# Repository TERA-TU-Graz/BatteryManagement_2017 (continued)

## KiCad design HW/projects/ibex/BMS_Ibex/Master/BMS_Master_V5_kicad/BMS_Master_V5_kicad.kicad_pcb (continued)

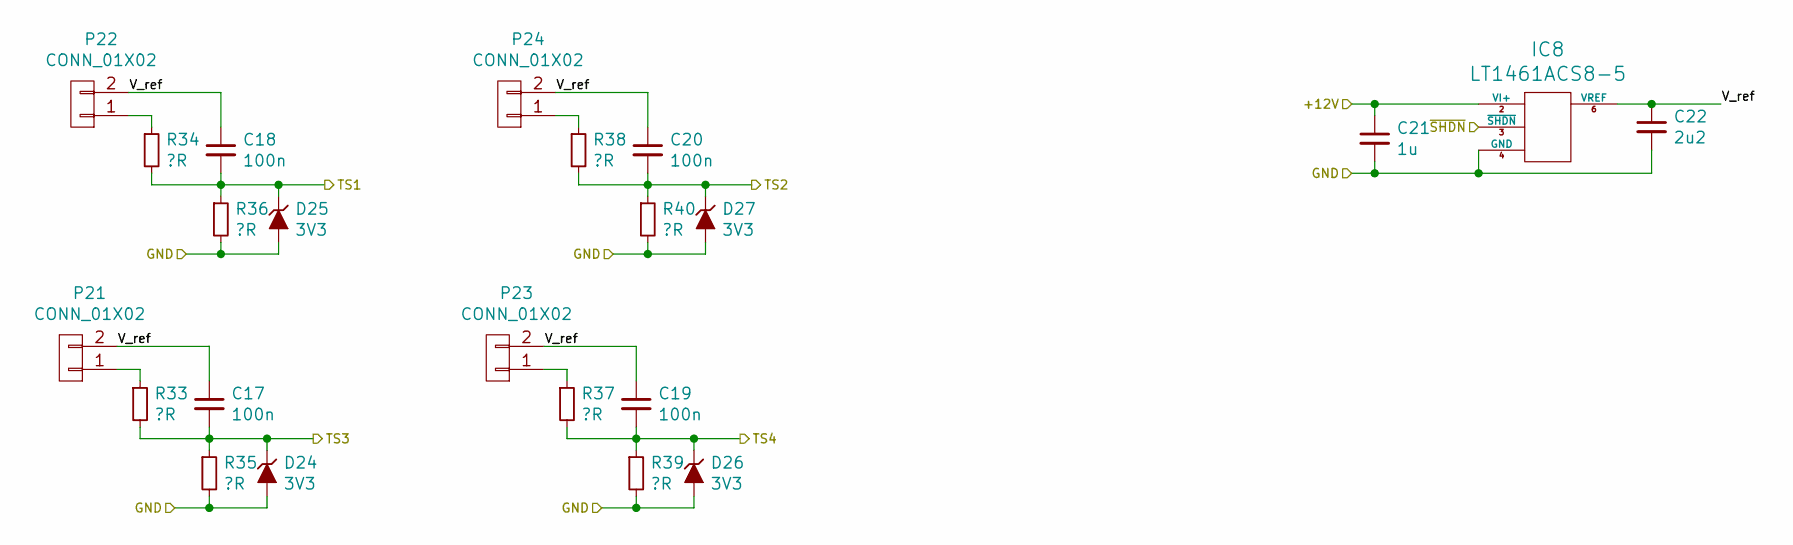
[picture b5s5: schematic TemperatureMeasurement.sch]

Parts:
C17, C18, C19, C20: 100n; C_0603
C21: 1u; C_0805
C22: 2u2; C_0805
D24, D25, D26, D27: 3V3; DO-216AA
IC8: LT1461ACS8-5; SOIC-8_3.9x4.9mm_Pitch1.27mm
P21, P22, P23, P24: CONN_01X02; Molex_PicoBlade_53398-0271
R33, R34, R35, R36, R37, R38, R39, R40: ?R; R_0603

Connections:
+12V: C21.1, IC8.2 (VI+); also elsewhere on the board
/TS1: C18.2, D25.1 (K), R34.2, R36.1; also elsewhere on the board
/TS2: C20.2, D27.1 (K), R38.2, R40.1; also elsewhere on the board
/TS3: C17.2, D24.1 (K), R33.2, R35.1; also elsewhere on the board
/TS4: C19.2, D26.1 (K), R37.2, R39.1; also elsewhere on the board
/TemperatureMeasurement/V_ref: C17.1, C18.1, C19.1, C20.1, C22.1, IC8.6 (VREF), P21.2, P22.2, P23.2, P24.2
/TemperatureMeasurement/~SHDN: IC8.3 (~SHDN); also elsewhere on the board
GND: C21.2, C22.2, D24.2 (A), D25.2 (A), D26.2 (A), D27.2 (A), IC8.4 (GND), R35.2, R36.2, R39.2, R40.2; also elsewhere on the board
unnamed: P21.1, R33.1
unnamed: P22.1, R34.1
unnamed: P23.1, R37.1
unnamed: P24.1, R38.1

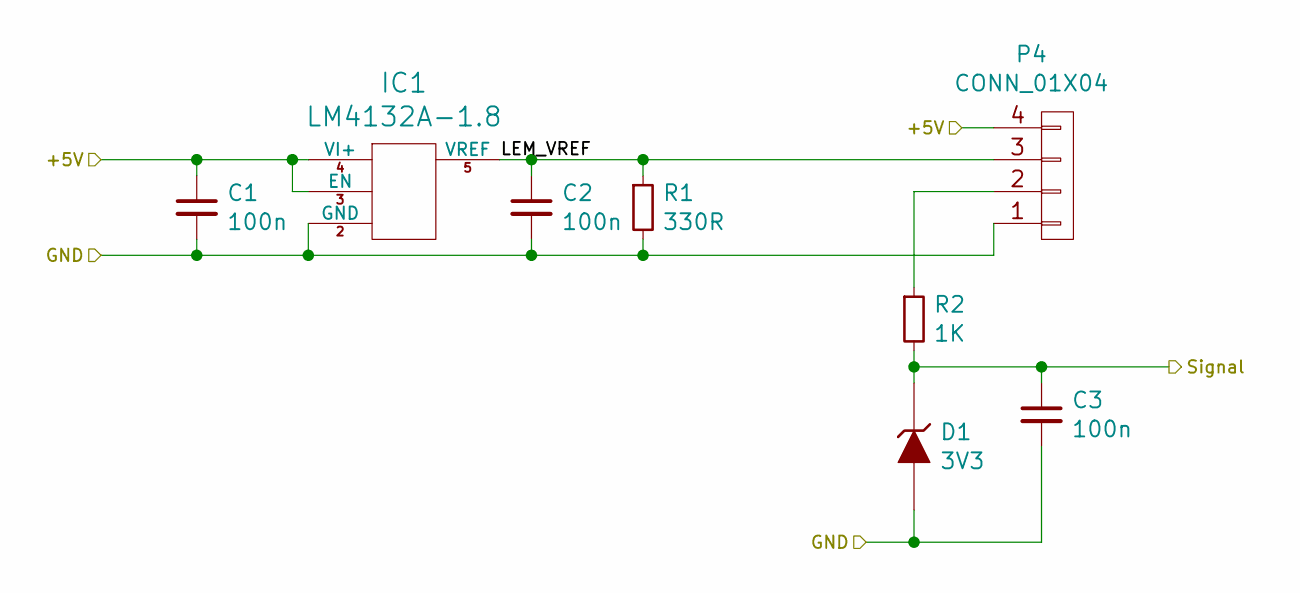
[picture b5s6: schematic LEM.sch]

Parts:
C1, C2, C3: 100n; C_0603
D1: 3V3; DO-216AA
IC1: LM4132A-1.8; SOT-23-5
P4: CONN_01X04; Molex_PicoBlade_53398-0471
R1: 330R; R_0603
R2: 1K; R_0805

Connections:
+5V: C1.1, IC1.3 (EN), IC1.4 (VI+), P4.4; also elsewhere on the board
/CurrentMeasurement/LEM1/LEM_VREF: C2.1, IC1.5 (VREF), P4.3, R1.1
/LEM1: C3.1, D1.1 (K), R2.2; also elsewhere on the board
GND: C1.2, C2.2, C3.2, D1.2 (A), IC1.2 (GND), P4.1, R1.2; also elsewhere on the board
unnamed: P4.2, R2.1

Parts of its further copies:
C4, C5, C6, C7, C8, C9: 100n; C_0603
D2, D3: 3V3; DO-216AA
IC2, IC3: LM4132A-1.8; SOT-23-5
P5, P6: CONN_01X04; Molex_PicoBlade_53398-0471
R3, R5: 330R; R_0603
R4, R6: 1K; R_0805

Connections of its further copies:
+5V: C4.1, C7.1, IC2.3 (EN), IC2.4 (VI+), IC3.3 (EN), IC3.4 (VI+), P5.4, P6.4; also elsewhere on the board
/CurrentMeasurement/LEM2/LEM_VREF: C5.1, IC2.5 (VREF), P5.3, R3.1
/CurrentMeasurement/LEM3/LEM_VREF: C8.1, IC3.5 (VREF), P6.3, R5.1
/LEM2: C6.1, D2.1 (K), R4.2; also elsewhere on the board
/LEM3: C9.1, D3.1 (K), R6.2; also elsewhere on the board
GND: C4.2, C5.2, C6.2, C7.2, C8.2, C9.2, D2.2 (A), D3.2 (A), IC2.2 (GND), IC3.2 (GND), P5.1, P6.1, R3.2, R5.2; also elsewhere on the board
unnamed: P5.2, R4.1
unnamed: P6.2, R6.1

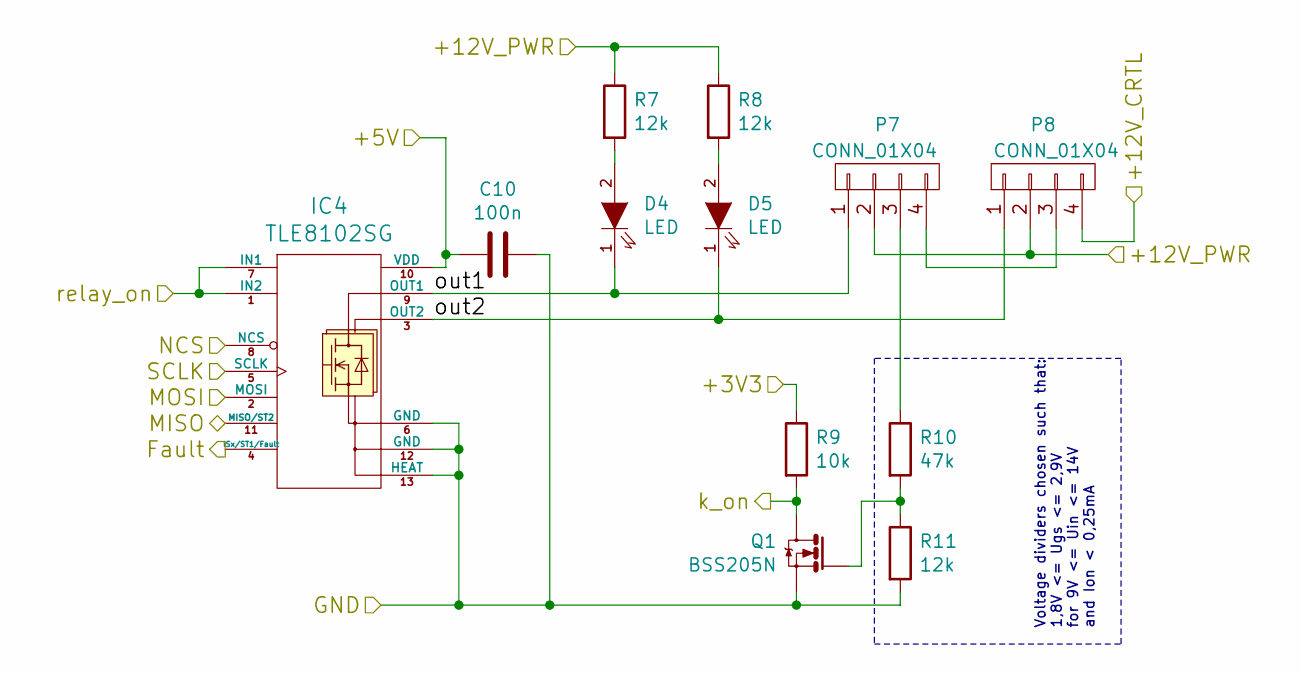
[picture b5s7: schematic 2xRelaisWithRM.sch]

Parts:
C10: 100n; C_0603
D4, D5: LED; LED_0805
IC4: TLE8102SG; INF-PG-DSO-12-11-EP_EPvias
P7, P8: CONN_01X04; JST_XH_B04B-XH-A_04x2.50mm_Straight
Q1: BSS205N; SOT-23
R7, R8, R11: 12k; R_0805
R9: 10k; R_0805
R10: 47k; R_0805

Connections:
+3V3: R9.1; also elsewhere on the board
+5V: C10.2, IC4.10 (VDD); also elsewhere on the board
+12L: P7.2, P8.2, R7.1, R8.1; also elsewhere on the board
+12V: P8.4; also elsewhere on the board
/Interlock_OK: IC4.1 (IN2), IC4.7 (IN1); also elsewhere on the board
/MISO: IC4.11 (MISO/ST2); also elsewhere on the board
/MOSI: IC4.2 (MOSI); also elsewhere on the board
/RelayAndFanCtrl/SuperChargerRelais/out1: D4.1 (K), IC4.9 (OUT1), P7.1
/RelayAndFanCtrl/SuperChargerRelais/out2: D5.1 (K), IC4.3 (OUT2), P8.1
/SCLK: IC4.5 (SCLK); also elsewhere on the board
/SPI_Controller/NCS7: IC4.8 (NCS); also elsewhere on the board
/SuperCharger_Fault: IC4.4 (ISx/ST1/Fault); also elsewhere on the board
/SuperCharger_ON: Q1.3 (D), R9.2; also elsewhere on the board
GND: C10.1, IC4.6 (GND), IC4.12 (GND), IC4.13 (HEAT), Q1.2 (S), R11.2; also elsewhere on the board
unnamed: D4.2 (A), R7.2
unnamed: D5.2 (A), R8.2
unnamed: P7.3, R10.1
unnamed: P7.4, P8.3
unnamed: Q1.1 (G), R10.2, R11.1

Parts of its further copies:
C11: 100n; C_0603
D6, D7: LED; LED_0805
IC5: TLE8102SG; INF-PG-DSO-12-11-EP_EPvias
P9, P10: CONN_01X04; JST_XH_B04B-XH-A_04x2.50mm_Straight
Q2: BSS205N; SOT-23
R12, R13, R16: 12k; R_0805
R14: 10k; R_0805
R15: 47k; R_0805

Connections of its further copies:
+3V3: R14.1; also elsewhere on the board
+5V: C11.2, IC5.10 (VDD); also elsewhere on the board
+12L: P9.2, P10.2, R12.1, R13.1; also elsewhere on the board
+12V: P10.4; also elsewhere on the board
/Interlock_OK: IC5.1 (IN2), IC5.7 (IN1); also elsewhere on the board
/MISO: IC5.11 (MISO/ST2); also elsewhere on the board
/MOSI: IC5.2 (MOSI); also elsewhere on the board
/Main_Fault: IC5.4 (ISx/ST1/Fault); also elsewhere on the board
/Main_On: Q2.3 (D), R14.2; also elsewhere on the board
/RelayAndFanCtrl/MainRelais/out1: D6.1 (K), IC5.9 (OUT1), P9.1
/RelayAndFanCtrl/MainRelais/out2: D7.1 (K), IC5.3 (OUT2), P10.1
/SCLK: IC5.5 (SCLK); also elsewhere on the board
/SPI_Controller/NCS6: IC5.8 (NCS); also elsewhere on the board
GND: C11.1, IC5.6 (GND), IC5.12 (GND), IC5.13 (HEAT), Q2.2 (S), R16.2; also elsewhere on the board
unnamed: D6.2 (A), R12.2
unnamed: D7.2 (A), R13.2
unnamed: P9.3, R15.1
unnamed: P9.4, P10.3
unnamed: Q2.1 (G), R15.2, R16.1

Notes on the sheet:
Voltage dividers chosen such that: 1,8V <= Ugs <= 2,9V for 9V <= Uin <= 14V and Ion < 0,25mA

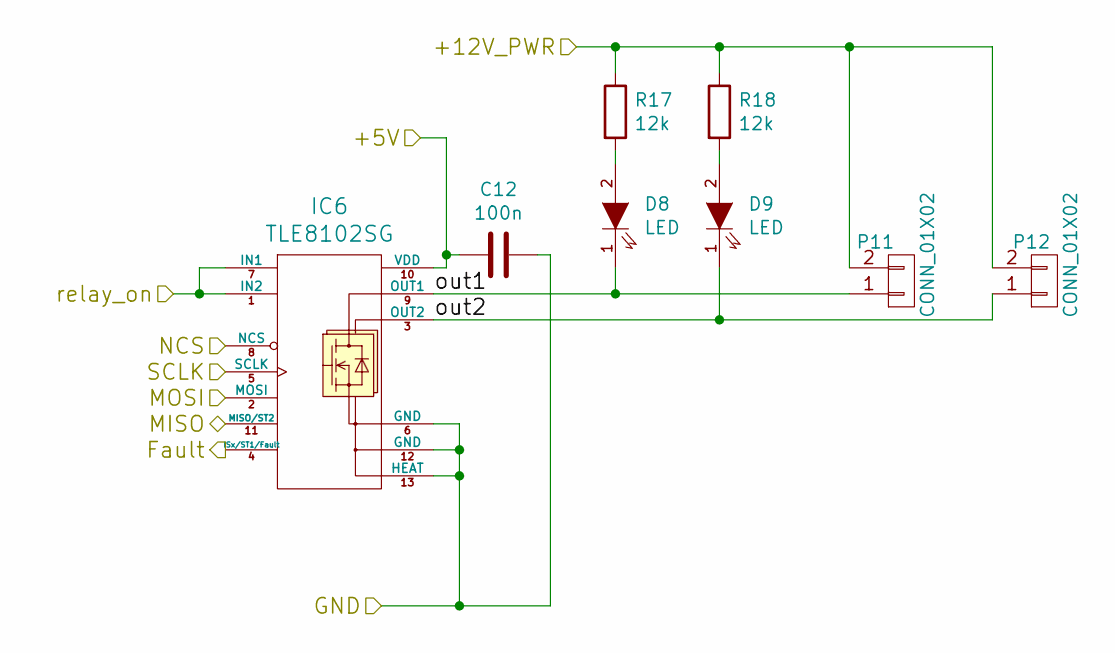
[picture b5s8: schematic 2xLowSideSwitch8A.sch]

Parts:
C12: 100n; C_0603
D8, D9: LED; LED_0805
IC6: TLE8102SG; INF-PG-DSO-12-11-EP_EPvias
P11, P12: CONN_01X02; JST_XH_B02B-XH-A_02x2.50mm_Straight
R17, R18: 12k; R_0805

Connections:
+5V: C12.2, IC6.10 (VDD); also elsewhere on the board
+12L: P11.2, P12.2, R17.1, R18.1; also elsewhere on the board
/Interlock_OK: IC6.1 (IN2), IC6.7 (IN1); also elsewhere on the board
/MISO: IC6.11 (MISO/ST2); also elsewhere on the board
/MOSI: IC6.2 (MOSI); also elsewhere on the board
/Precharge_Fault: IC6.4 (ISx/ST1/Fault); also elsewhere on the board
/RelayAndFanCtrl/PRECHARGER/out1: D8.1 (K), IC6.9 (OUT1), P11.1
/RelayAndFanCtrl/PRECHARGER/out2: D9.1 (K), IC6.3 (OUT2), P12.1
/SCLK: IC6.5 (SCLK); also elsewhere on the board
/SPI_Controller/NCS8: IC6.8 (NCS); also elsewhere on the board
GND: C12.1, IC6.6 (GND), IC6.12 (GND), IC6.13 (HEAT); also elsewhere on the board
unnamed: D8.2 (A), R17.2
unnamed: D9.2 (A), R18.2

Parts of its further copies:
C13: 100n; C_0603
D10, D11: LED; LED_0805
IC7: TLE8102SG; INF-PG-DSO-12-11-EP_EPvias
P13, P14: CONN_01X02; JST_XH_B02B-XH-A_02x2.50mm_Straight
R19, R20: 12k; R_0805

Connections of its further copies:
+5V: C13.2, IC7.10 (VDD); also elsewhere on the board
+12L: P13.2, P14.2, R19.1, R20.1; also elsewhere on the board
/FAN_Fault: IC7.4 (ISx/ST1/Fault); also elsewhere on the board
/FAN_PWM: IC7.1 (IN2), IC7.7 (IN1); also elsewhere on the board
/MISO: IC7.11 (MISO/ST2); also elsewhere on the board
/MOSI: IC7.2 (MOSI); also elsewhere on the board
/RelayAndFanCtrl/FANS/out1: D10.1 (K), IC7.9 (OUT1), P13.1
/RelayAndFanCtrl/FANS/out2: D11.1 (K), IC7.3 (OUT2), P14.1
/SCLK: IC7.5 (SCLK); also elsewhere on the board
/SPI_Controller/NCS5: IC7.8 (NCS); also elsewhere on the board
GND: C13.1, IC7.6 (GND), IC7.12 (GND), IC7.13 (HEAT); also elsewhere on the board
unnamed: D10.2 (A), R19.2
unnamed: D11.2 (A), R20.2

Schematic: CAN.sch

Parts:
C15: 47nF; C_0805
C23: 100n; C_0805
D12, D13: SUPPRESSOR; SOT-23
JP7, JP8: Jumper_NO_Small; SOLDERJUMPER_2
L1: CM_CHOKE; ACT45B-510-2P-TL003
P17: CAN_CON; CIOC_4-1-FV
R23: 56k; R_0805
R24, R25: 60R; R_0805
S1: SWITCH_02x2POS; TE_1825360-1
U3: SN65HVD230; SOIC-8_3.9x4.9mm_Pitch1.27mm

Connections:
/CAN1_RS: R23.2; also elsewhere on the board
/CAN1_RXD: U3.4 (RXD); also elsewhere on the board
/CAN1_TXD: U3.1 (TXD); also elsewhere on the board
/CAN_connect/CAN1/CAN+: D12.2 (Pin2), JP7.1, L1.3 (SA), U3.7 (CANH); also elsewhere on the board
/CAN_connect/CAN1/CAN-: D12.1 (Pin1), JP8.1, L1.2 (AB), U3.6 (CANL); also elsewhere on the board
/CAN_connect/CAN1/CAN_supply: C23.1, U3.3 (VCC); also elsewhere on the board
/CAN_connect/CAN1/CANperi+: D13.2 (Pin2), JP7.2, L1.4 (SB), P17.3 (CAN_H), S1.4
/CAN_connect/CAN1/CANperi-: D13.1 (Pin1), JP8.2, L1.1 (AA), P17.2 (CAN_L), S1.3
GND: C15.2, C23.2, D12.3 (Pin3), D13.3 (Pin3), P17.1 (GND), U3.2 (GND); also elsewhere on the board
unnamed: C15.1, R24.2, R25.2
unnamed: R23.1, U3.8 (Rs(Mode))
unnamed: R24.1, S1.1
unnamed: R25.1, S1.2

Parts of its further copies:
C16: 47nF; C_0805
C24: 100n; C_0805
D14, D15: SUPPRESSOR; SOT-23
JP9, JP10: Jumper_NO_Small; SOLDERJUMPER_2
L2: CM_CHOKE; ACT45B-510-2P-TL003
P18: CAN_CON; CIOC_4-1-FV
R26: 56k; R_0805
R27, R28: 60R; R_0805
S2: SWITCH_02x2POS; TE_1825360-1
U4: SN65HVD230; SOIC-8_3.9x4.9mm_Pitch1.27mm

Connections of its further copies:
+3V3: C24.1, U4.3 (VCC); also elsewhere on the board
/CAN2_RS: R26.2; also elsewhere on the board
/CAN2_RXD: U4.4 (RXD); also elsewhere on the board
/CAN2_TXD: U4.1 (TXD); also elsewhere on the board
/CAN_connect/CAN2/CAN+: D14.2 (Pin2), JP9.1, L2.3 (SA), U4.7 (CANH)
/CAN_connect/CAN2/CAN-: D14.1 (Pin1), JP10.1, L2.2 (AB), U4.6 (CANL)
/CAN_connect/CAN2/CANperi+: D15.2 (Pin2), JP9.2, L2.4 (SB), P18.3 (CAN_H), S2.4
/CAN_connect/CAN2/CANperi-: D15.1 (Pin1), JP10.2, L2.1 (AA), P18.2 (CAN_L), S2.3
GND: C16.2, C24.2, D14.3 (Pin3), D15.3 (Pin3), P18.1 (GND), U4.2 (GND); also elsewhere on the board
unnamed: C16.1, R27.2, R28.2
unnamed: R26.1, U4.8 (Rs(Mode))
unnamed: R27.1, S2.1
unnamed: R28.1, S2.2

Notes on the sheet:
RS(Mode): GND (Logic L) = Tranceiver on 3V3 (Logic H) = Tranceiver in power safe (standby = receive only)
Connection used for on board can tranceiver. (optional)
Place everything near the connector. (Exception CAN Tranceiver: this should be near STM)
keep this wires short

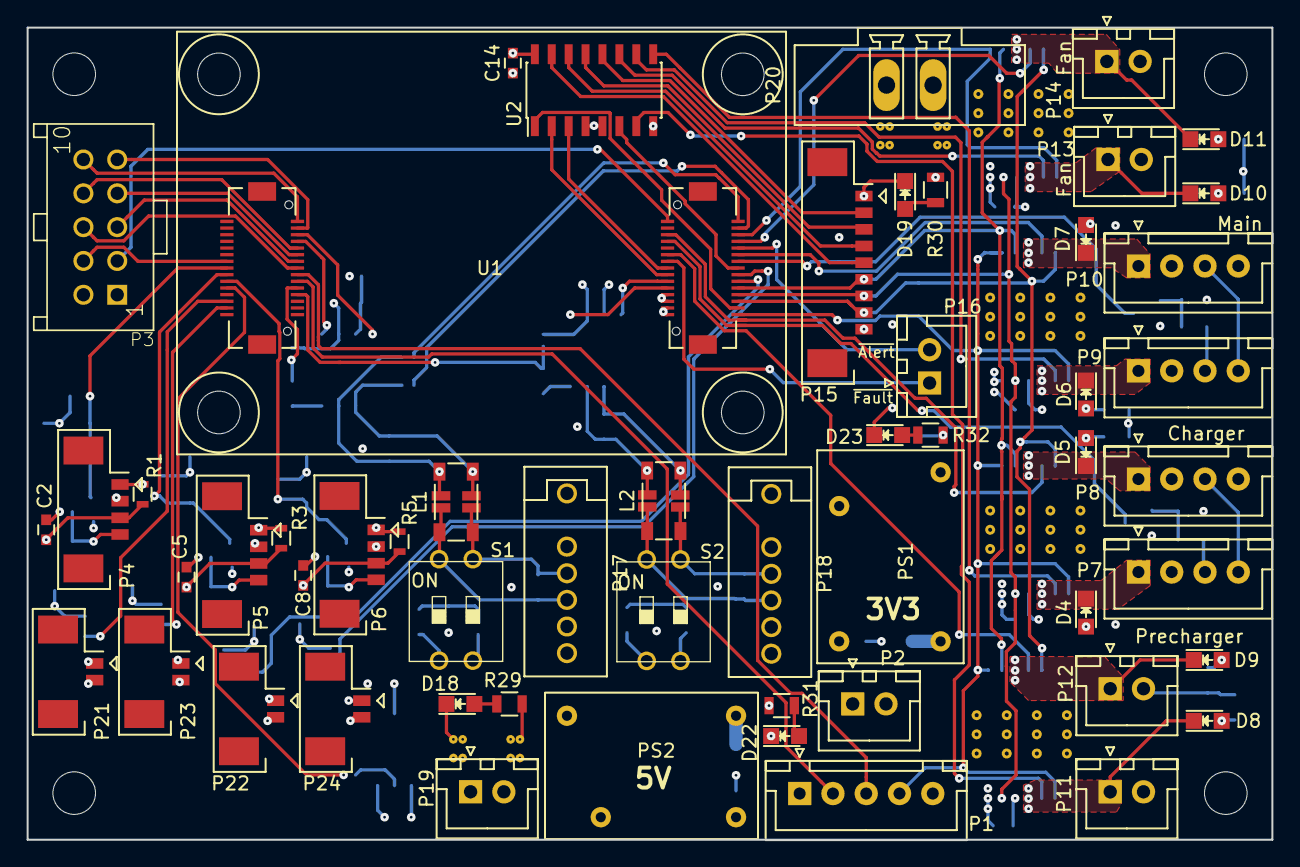
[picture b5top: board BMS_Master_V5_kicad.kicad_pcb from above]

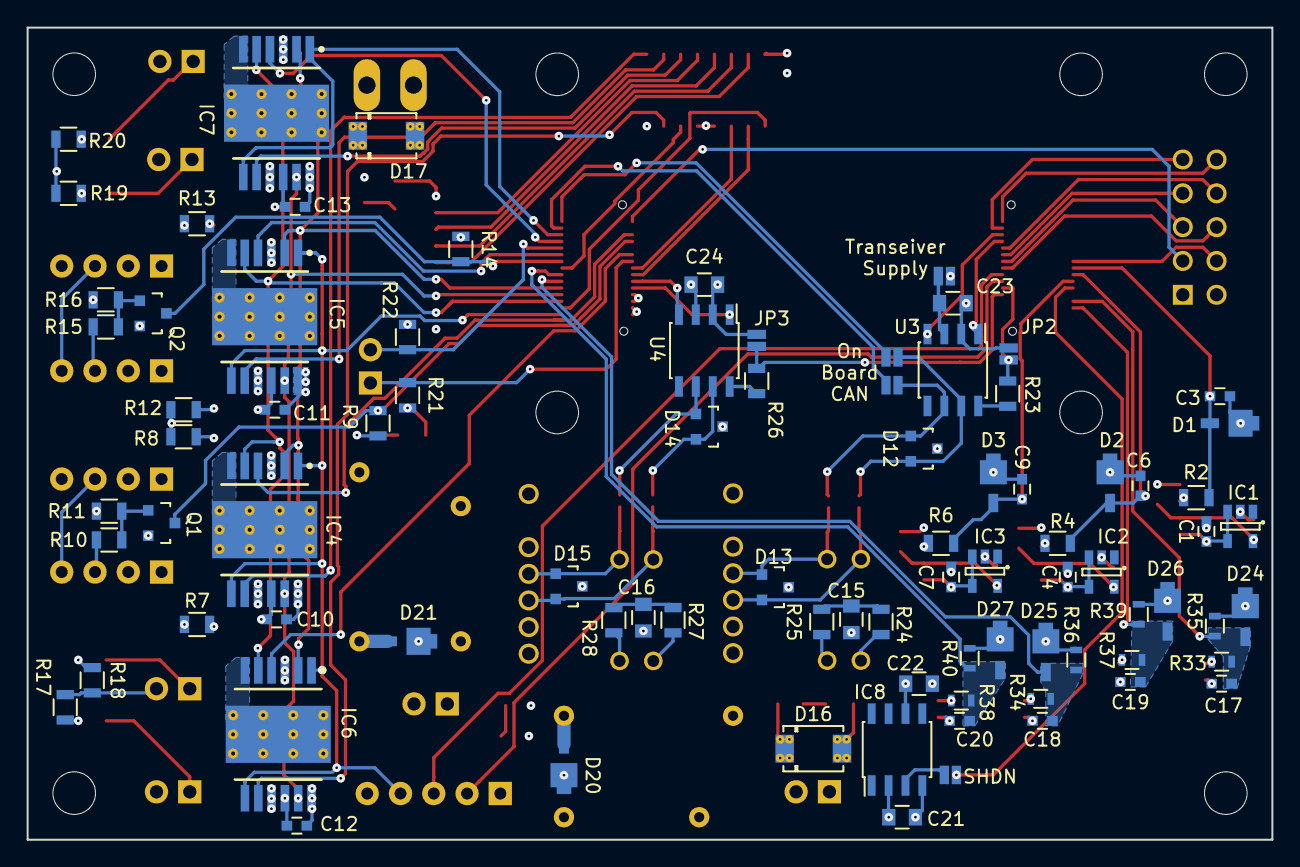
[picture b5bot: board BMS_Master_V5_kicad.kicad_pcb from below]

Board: 4 copper layers, 93.5 x 61.0 mm, 145 parts (86 on the bottom side), 111 nets.

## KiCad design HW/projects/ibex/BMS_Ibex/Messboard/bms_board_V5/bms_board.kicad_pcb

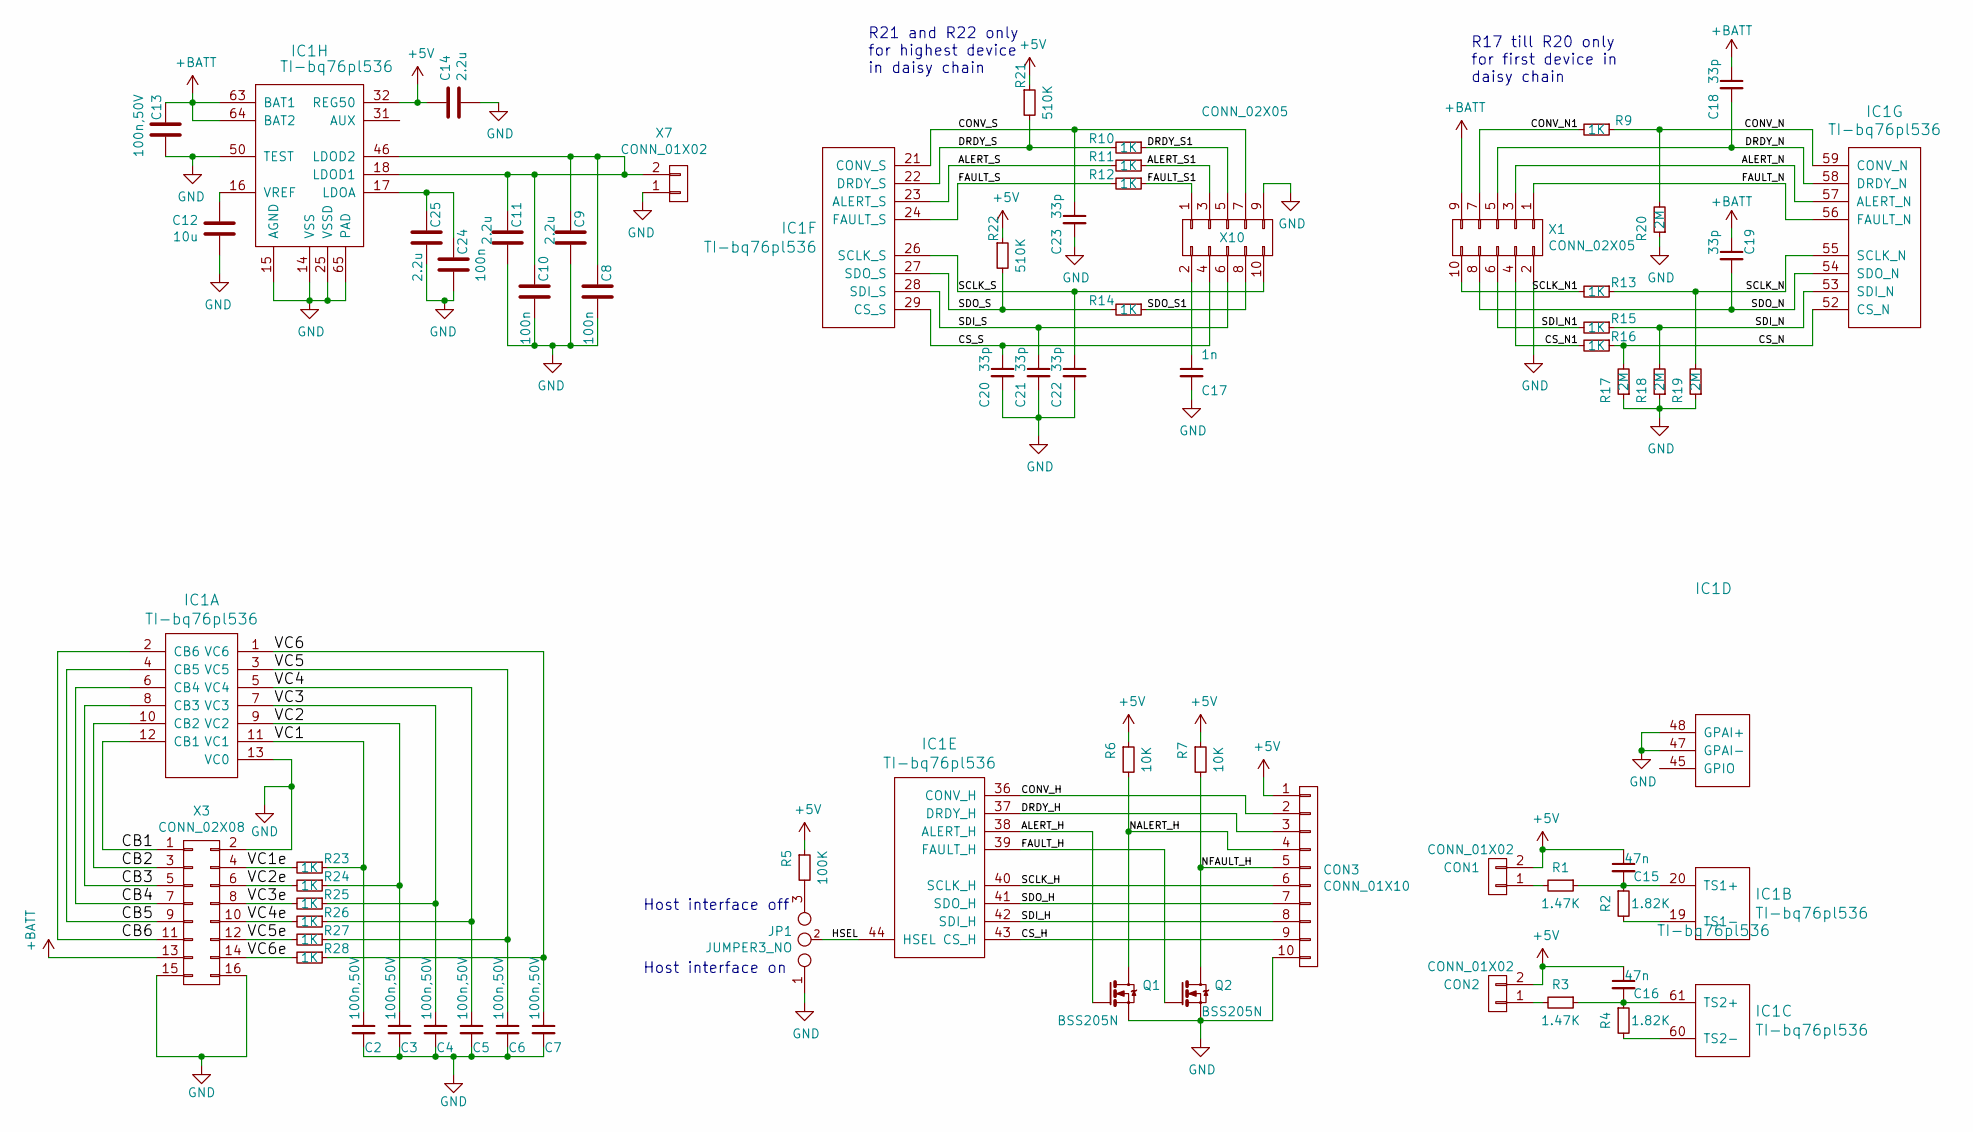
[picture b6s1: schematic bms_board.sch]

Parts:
C2, C3, C4, C5, C6, C7, C13: 100n,50V; C_0805
C8, C10, C24: 100n; C_0603
C9, C11, C14, C25: 2.2u; C_0805
C12: 10u; C_0805
C15, C16: 47n; C_0603
C17: 1n; C_0603
C18, C19, C20, C21, C22, C23: 33p; C_0603
CON1, CON2: CONN_01X02; Connector_Molex_PicoBlade_53398-0271
CON3: CONN_01X10; Connector_Molex_PicoBlade_53261-1071
IC1: TI-bq76pl536; TQFP-64_10x10mm_Pitch0.5mm_ThermalPad
JP1: JUMPER3_NO; SOLDERJUMPER_3
Q1, Q2: BSS205N; SOT-23
R1, R3: 1.47K; R_0603
R2, R4: 1.82K; R_0603
R5: 100K; R_0603
R6, R7: 10K; R_0603
R9, R10, R11, R12, R13, R14, R15, R16, R23, R24, R25, R26, R27, R28: 1K; R_0603
R17, R18, R19, R20: 2M; R_0603
R21, R22: 510K; R_0603
X1, X10: CONN_02X05; IDC_02X05_Angled
X3: CONN_02X08; Socket_Strip_Straight_2x08
X7: CONN_01X02; Socket_Strip_Straight_1x02

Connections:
+5V: C14.1, C15.1, C16.1, CON1.2, CON2.2, CON3.1, IC1.32 (REG50), R5.1, R6.1, R7.1, R21.1, R22.1
+BATT: C13.2, C18.1, C19.1, IC1.63 (BAT1), IC1.64 (BAT2), X1.9, X3.13
/ALERT_H: IC1.38 (ALERT_H), Q1.1 (G)
/ALERT_N: IC1.57 (ALERT_N), X1.3
/ALERT_S: IC1.23 (ALERT_S), R11.2
/ALERT_S1: R11.1, X10.3
/CB1: IC1.12 (CB1), X3.1
/CB2: IC1.10 (CB2), X3.3
/CB3: IC1.8 (CB3), X3.5
/CB4: IC1.6 (CB4), X3.7
/CB5: IC1.4 (CB5), X3.9
/CB6: IC1.2 (CB6), X3.11
/CONV_H: CON3.2, IC1.36 (CONV_H)
/CONV_N: IC1.59 (CONV_N), R9.1, R20.2
/CONV_N1: R9.2, X1.7
/CONV_S: C23.1, IC1.21 (CONV_S), X10.7
/CS_H: CON3.9, IC1.43 (CS_H)
/CS_N: IC1.52 (CS_N), R16.1, R17.2
/CS_N1: R16.2, X1.4
/CS_S: C20.1, IC1.29 (CS_S), X10.4
/DRDY_H: CON3.3, IC1.37 (DRDY_H)
/DRDY_N: C18.2, IC1.58 (DRDY_N), X1.5
/DRDY_S: IC1.22 (DRDY_S), R10.2, R21.2
/DRDY_S1: R10.1, X10.5
/FAULT_H: IC1.39 (FAULT_H), Q2.1 (G)
/FAULT_N: IC1.56 (FAULT_N), X1.1
/FAULT_S: IC1.24 (FAULT_S), R12.2
/FAULT_S1: R12.1, X10.1
/HSEL: IC1.44 (HSEL), JP1.2
/NALERT_H: CON3.4, Q1.3 (D), R6.2
/NFAULT_H: CON3.5, Q2.3 (D), R7.2
/SCLK_H: CON3.6, IC1.40 (SCLK_H)
/SCLK_N: IC1.55 (SCLK_N), R13.1, R19.2
/SCLK_N1: R13.2, X1.10
/SCLK_S: C22.1, IC1.26 (SCLK_S), X10.10
/SDI_H: CON3.8, IC1.42 (SDI_H)
/SDI_N: IC1.53 (SDI_N), R15.1, R18.2
/SDI_N1: R15.2, X1.6
/SDI_S: C21.1, IC1.28 (SDI_S), X10.6
/SDO_H: CON3.7, IC1.41 (SDO_H)
/SDO_N: C19.2, IC1.54 (SDO_N), X1.8
/SDO_S: IC1.27 (SDO_S), R14.2, R22.2
/SDO_S1: R14.1, X10.8
/VC1: C2.1, IC1.11 (VC1), R23.1
/VC1e: R23.2, X3.4
/VC2: C3.1, IC1.9 (VC2), R24.1
/VC2e: R24.2, X3.6
/VC3: C4.1, IC1.7 (VC3), R25.1
/VC3e: R25.2, X3.8
/VC4: C5.1, IC1.5 (VC4), R26.1
/VC4e: R26.2, X3.10
/VC5: C6.1, IC1.3 (VC5), R27.1
/VC5e: R27.2, X3.12
/VC6: C7.1, IC1.1 (VC6), R28.1
/VC6e: R28.2, X3.14
GND: C2.2, C3.2, C4.2, C5.2, C6.2, C7.2, C8.2, C9.2, C10.2, C11.2, C12.2, C13.1, C14.2, C17.2, C20.2, C21.2, C22.2, C23.2, C24.2, C25.2, CON3.10, IC1.13 (VC0), IC1.14 (VSS), IC1.15 (AGND), IC1.25 (VSSD), IC1.33 (VSS), IC1.34 (VSS), IC1.35 (VSS), IC1.47 (GPAI-), IC1.48 (GPAI+), IC1.49 (VSSD), IC1.50 (TEST), IC1.65 (PAD), JP1.1 (m), Q1.2 (S), Q2.2 (S), R17.1, R18.1, R19.1, R20.1, X1.2, X3.2, X3.15, X3.16, X7.1, X10.9
unnamed: C8.1, C9.1, C10.1, C11.1, IC1.18 (LDOD1), IC1.46 (LDOD2), X7.2
unnamed: C12.1, IC1.16 (VREF)
unnamed: C15.2, IC1.20 (TS1+), R1.1, R2.1
unnamed: C16.2, IC1.61 (TS2+), R3.1, R4.1
unnamed: C17.1, X10.2
unnamed: C24.1, C25.1, IC1.17 (LDOA)
unnamed: CON1.1, R1.2
unnamed: CON2.1, R3.2
unnamed: IC1.19 (TS1-), R2.2
unnamed: IC1.60 (TS2-), R4.2
unnamed: JP1.3, R5.2

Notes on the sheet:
R21 and R22 only for highest device in daisy chain
R17 till R20 only for first device in daisy chain
Host interface on
Host interface off

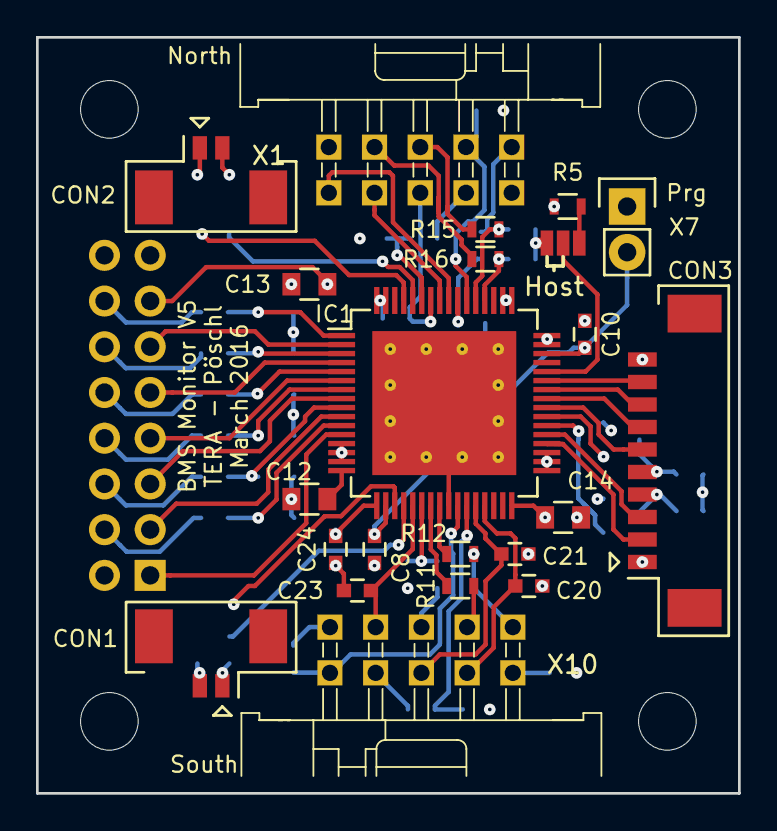
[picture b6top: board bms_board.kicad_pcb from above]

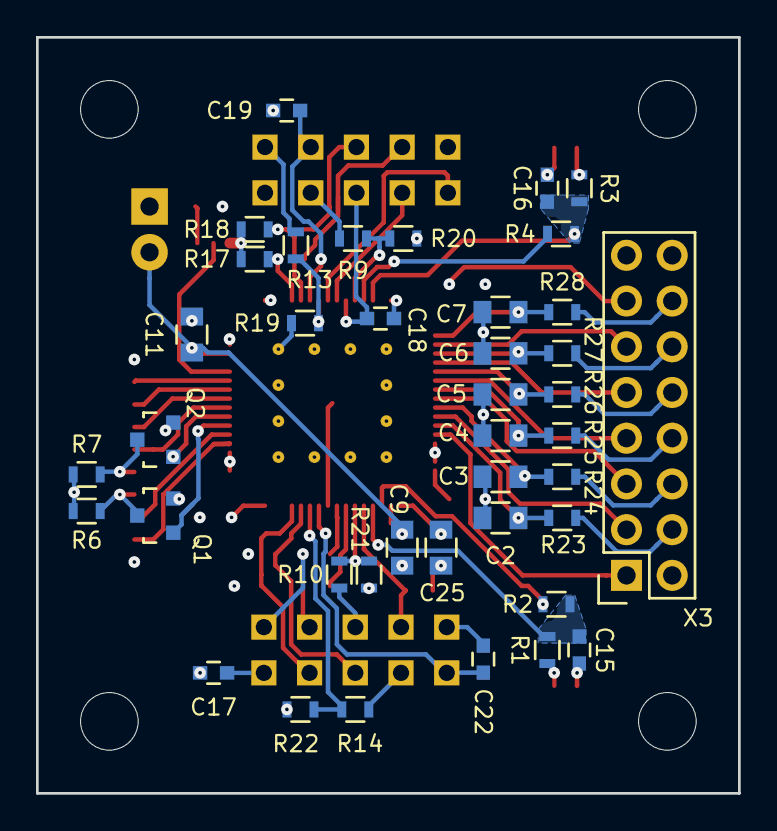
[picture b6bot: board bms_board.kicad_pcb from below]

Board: 4 copper layers, 39.0 x 42.0 mm, 62 parts (40 on the bottom side), 67 nets.
